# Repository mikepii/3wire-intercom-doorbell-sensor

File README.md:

Circuit (KiCad project) to detect door chime or warble tone from a IA543, PK543A, or similar
apartment intercom amplifier.
To be wired in parallel with apartment intercom.

Inputs: X and 1 from intercom.

Outputs: dry contact relay (normally-open and normally-closed terminals),
e.g. for detection by a Shelly smart switch.

Mounting: three holes for DIN rail mounting bracket Phoenix Contact 1201578.

You can order the PCB from a fabricator such as [OSH Park](https://oshpark.com/)
by uploading the zip of gerber/drill files (see Releases on GitHub).
You can also order it fully assembled from fabricators providing assembly service
by sending them the Bill of Materials (BOM) file along with that zip.

Based on information from [this post by Chris Whong](https://chris-m-whong.medium.com/connecting-an-apartment-door-buzzer-to-a-smarthome-hub-4664cf6a3ce4).
This board provides the same functionality as the discontinued Alpha Communications RY014B.

## Development notes

Panelize with KiKit:

```sh
kikit panelize \
    --layout 'hspace: 0.5mm; vspace: 0.5mm; cols: 2' \
    --tabs 'type: fixed; vcount: 4; hcount: 4' \
    --cuts 'type: mousebites' \
    $(pwd)'/doorbellsensor.kicad_pcb' $(pwd)'/panelized/doorbellsensor_panelized.kicad_pcb'
```

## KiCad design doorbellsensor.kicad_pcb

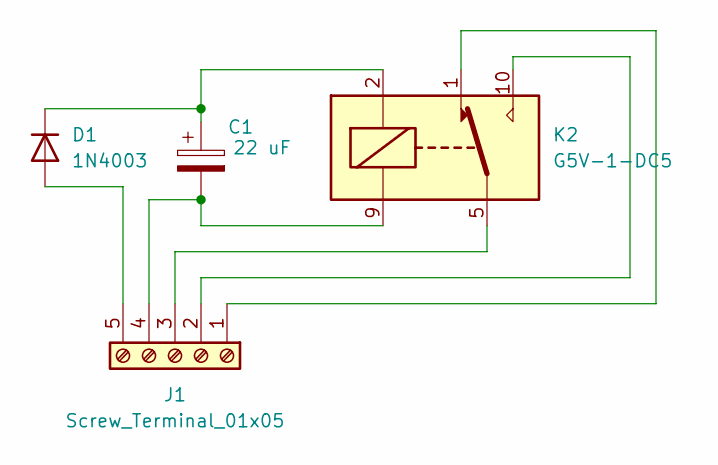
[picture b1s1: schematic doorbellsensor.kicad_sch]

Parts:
C1: 22 uF; CP_Radial_D5.0mm_P2.50mm; MPN EEU-EB1H220SH
D1: 1N4003; D_DO-41_SOD81_P10.16mm_Horizontal; MPN 1N4003
J1: Screw_Terminal_01x05; TerminalBlock_Phoenix_MKDS-1,5-5_1x05_P5.00mm_Horizontal; MPN 1715187
K2: G5V-1-DC5; Relay_SPDT_Omron_G5V-1; MPN G5V-1-DC5

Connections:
unnamed: D1.2 (A), J1.5
unnamed: C1.1, D1.1 (K), K2.2
unnamed: J1.1, K2.1
unnamed: J1.2, K2.10
unnamed: J1.3, K2.5, K2.6
unnamed: C1.2, J1.4, K2.9

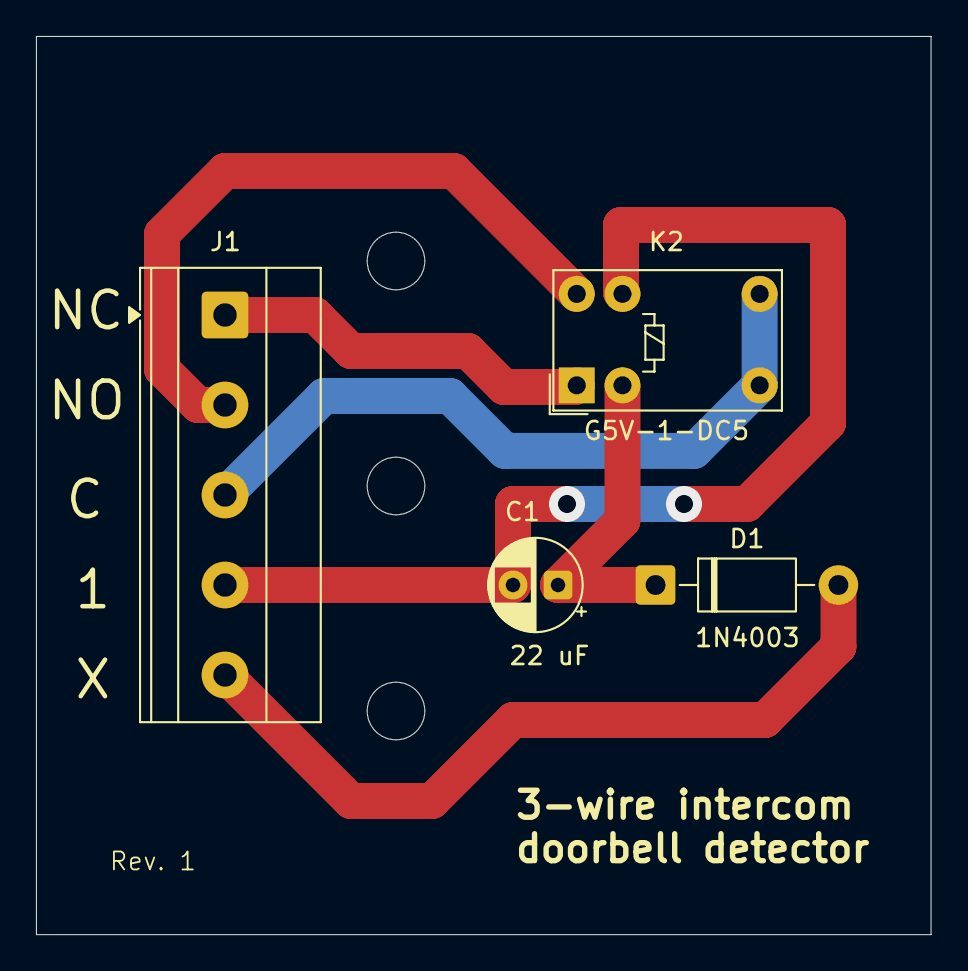
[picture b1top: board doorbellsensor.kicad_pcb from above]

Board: 2 copper layers, 49.7 x 49.9 mm, 4 parts (0 on the bottom side), 6 nets.

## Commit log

2026-03-25 rev 0
2026-03-26 document kikit panelize command
2026-03-26 rev 1 - silkscreen improvements
2026-03-26 describe project in readme
2026-06-30 Update project description to include IA543 model
